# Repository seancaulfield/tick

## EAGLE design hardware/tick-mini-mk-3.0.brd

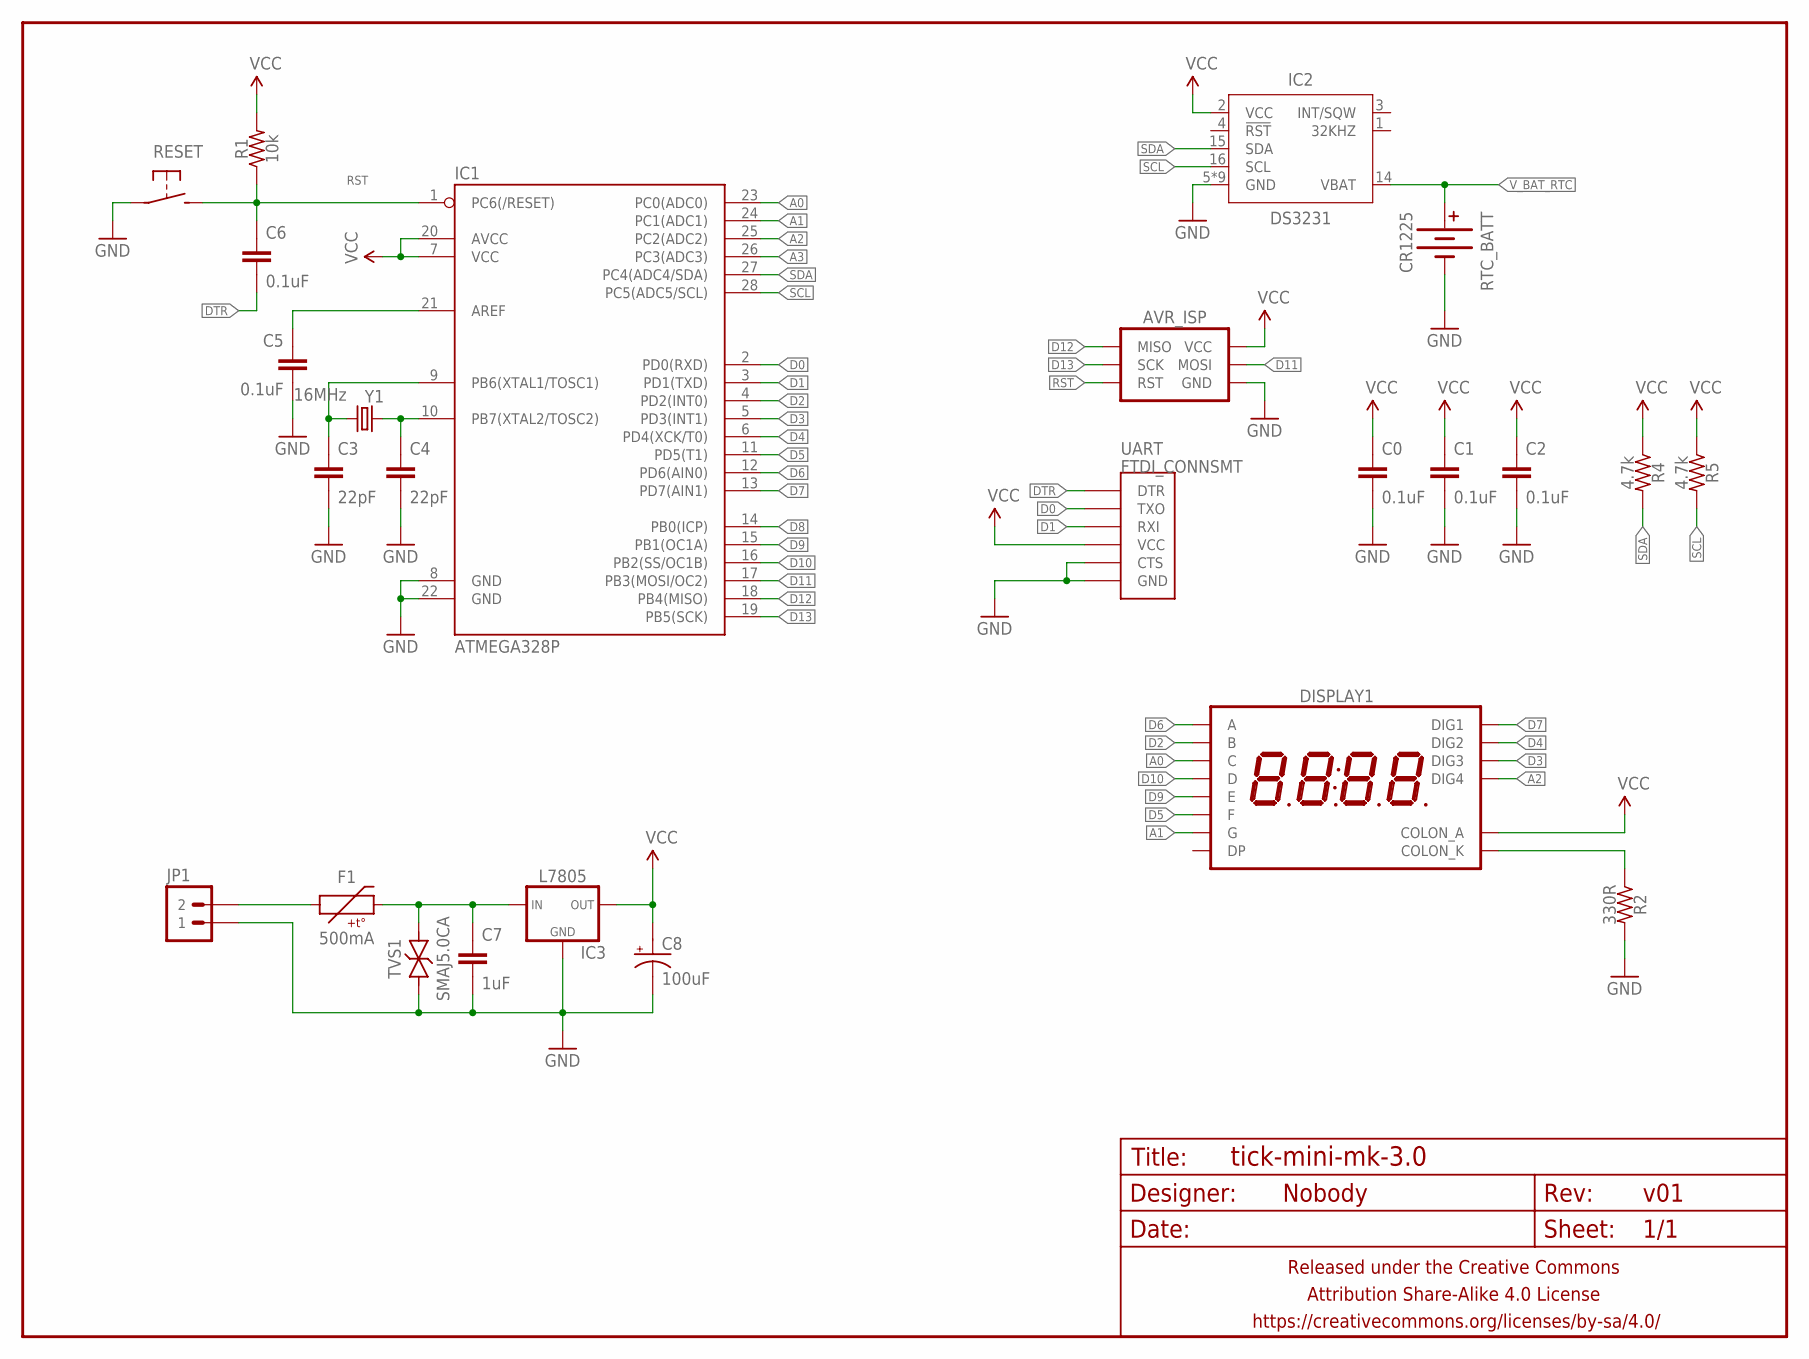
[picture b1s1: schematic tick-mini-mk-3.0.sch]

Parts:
AVR_ISP: AVR_SPI_PRG_6PTH; 2X3
C0, C1, C2, C5, C6: 0.1uF; C0603
C3, C4: 22pF; C0603
C7: 1uF; C0805
C8: 100uF; E2,5-5
DISPLAY1: 7SEG_4DIGIT_COLON14.2MM-CC-NS; 7SEG_4DIG_NS
F1: 500mA; PTC-1206
FRAME1: FRAME-LETTERNO_PACKAGE; DUMMY
IC1: ATMEGA328P; DIL28-3
IC2: DS3231; SO16W
IC3: L7805; SO08
JP1: M02PTH-CENTERED-R+; 1X02-CENTER-R+
R1: 10k; R0603
R2: 330R; RESISTOR-AXIAL-PTH-7.62MM
R4, R5: 4.7k; R0603
RESET: SPST-NO-TACT3MM-PTH-SMALL-PADS; DTS-3-SMALL-PADS
RTC_BATT: CR1225; BATTCON_12MM
TVS1: SMAJ5.0CA; SMA-DIODE-TVS-BIDIR
UART: FTDI_CONNSMT; FTDI_CONN_SMT
Y1: 16MHz; HC49U-V

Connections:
A0: DISPLAY1.P$4 (C), IC1.23 (PC0(ADC0))
A1: DISPLAY1.P$5 (G), IC1.24 (PC1(ADC1))
A2: DISPLAY1.P$6 (DIG4), IC1.25 (PC2(ADC2))
A3: IC1.26 (PC3(ADC3))
D0: IC1.2 (PD0(RXD)), UART.TXO
D1: IC1.3 (PD1(TXD)), UART.RXI
D2: DISPLAY1.P$9 (B), IC1.4 (PD2(INT0))
D3: DISPLAY1.P$10 (DIG3), IC1.5 (PD3(INT1))
D4: DISPLAY1.P$11 (DIG2), IC1.6 (PD4(XCK/T0))
D5: DISPLAY1.P$12 (F), IC1.11 (PD5(T1))
D6: DISPLAY1.P$13 (A), IC1.12 (PD6(AIN0))
D7: DISPLAY1.P$14 (DIG1), IC1.13 (PD7(AIN1))
D8: IC1.14 (PB0(ICP))
D9: DISPLAY1.P$1 (E), IC1.15 (PB1(OC1A))
D10: DISPLAY1.P$2 (D), IC1.16 (PB2(SS/OC1B))
D11: AVR_ISP.4 (MOSI), IC1.17 (PB3(MOSI/OC2))
D12: AVR_ISP.1 (MISO), IC1.18 (PB4(MISO))
D13: AVR_ISP.3 (SCK), IC1.19 (PB5(SCK))
DTR: C6.2, UART.DTR
GND: AVR_ISP.6 (GND), C0.2, C1.2, C2.2, C3.2, C4.2, C5.2, C7.2, C8.-, IC1.8 (GND), IC1.22 (GND), IC2.5 (GND), IC2.6 (GND), IC2.7 (GND), IC2.8 (GND), IC2.9 (GND), IC2.10 (GND), IC2.11 (GND), IC2.12 (GND), IC2.13 (GND), IC3.2 (GND), IC3.3 (GND), IC3.4 (GND), IC3.5 (GND), IC3.6 (GND), IC3.7 (GND), JP1.1, R2.P$2 (2), RESET.1, RTC_BATT.GND (-), TVS1.1, UART.CTS, UART.GND
unnamed: C4.1, IC1.10 (PB7(XTAL2/TOSC2)), Y1.1
unnamed: C3.1, IC1.9 (PB6(XTAL1/TOSC1)), Y1.2
unnamed: C5.1, IC1.21 (AREF)
unnamed: DISPLAY1.P$7 (COLON_K), R2.P$1 (1)
unnamed: F1.1, JP1.2
unnamed: C7.1, F1.2, IC3.8 (IN), TVS1.2
RST: AVR_ISP.5 (RST), C6.1, IC1.1 (PC6(/RESET)), R1.1, RESET.2
SCL: IC1.28 (PC5(ADC5/SCL)), IC2.16 (SCL), R5.2
SDA: IC1.27 (PC4(ADC4/SDA)), IC2.15 (SDA), R4.2
VCC: AVR_ISP.2 (VCC), C0.1, C1.1, C2.1, C8.+, DISPLAY1.P$8 (COLON_A), IC1.7 (VCC), IC1.20 (AVCC), IC2.2 (VCC), IC3.1 (OUT), R1.2, R4.1, R5.1, UART.VCC
V_BAT_RTC: IC2.14 (VBAT), RTC_BATT.PWR@1 (+)

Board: 2 copper layers, 26 parts (2 on the bottom side), 29 nets, no tracks yet.

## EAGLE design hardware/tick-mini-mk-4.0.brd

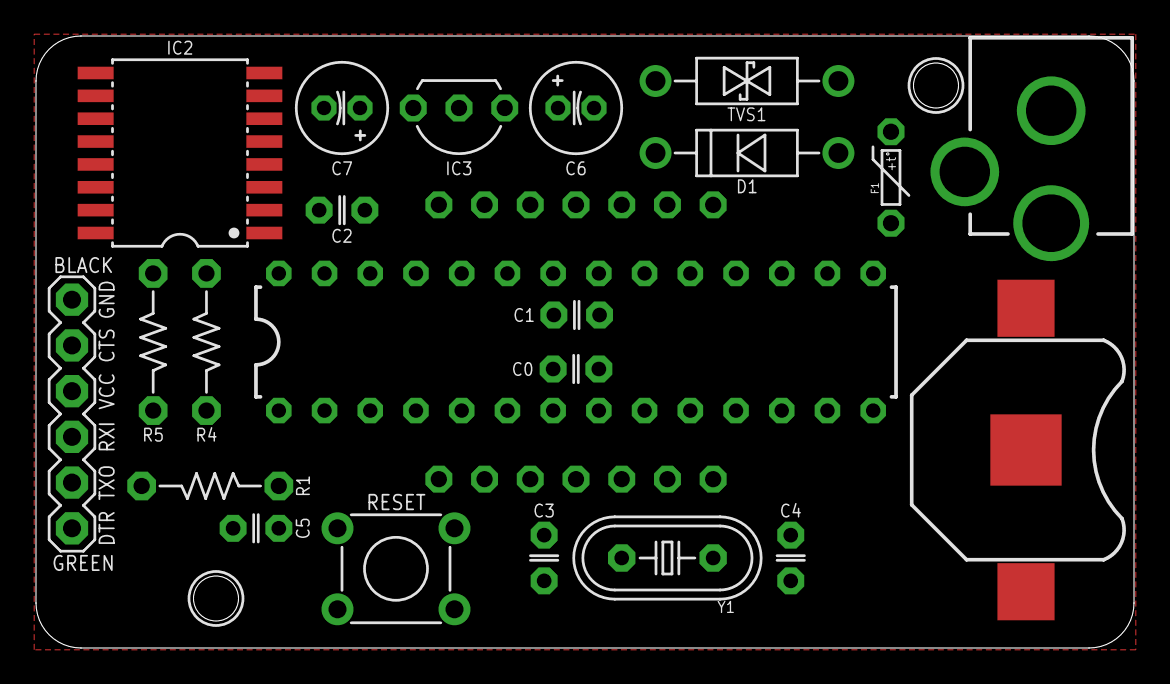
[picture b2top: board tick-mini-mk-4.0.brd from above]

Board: 2 copper layers, 61.0 x 34.0 mm, 24 parts (0 on the bottom side), 27 nets, no tracks yet.

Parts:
C0, C1, C2, C5: 0.1uF; C025-024X044
C3, C4: 22pF; C025-024X044
C6, C7: 10uF; E2-5
D1: 1N5819; DIODE-10.16MM
DISPLAY1: 7SEG_4DIGIT_COLON14.2MM-CC-NS; 7SEG_4DIG_NS
F1: 500mA; PTC-PTH-5.08MM
FRAME1: FRAME-LETTERNO_PACKAGE; DUMMY
IC1: ATMEGA328P; DIL28-3
IC2: DS3231; SO16W
IC3: L7805; TO-92-AMMO
PWR1: DCBARRELPTH; DCJACK_2MM_PTH
R1: 10k; RESISTOR-AXIAL-PTH-7.62MM
R4, R5: 4.7k; RESISTOR-AXIAL-PTH-7.62MM
RESET: SPST-NO-TACT6MM-PTH-SMALL-PADS; DTS-6-SMALL-PADS
RTC_BATT: CR1225; BATTCON_12MM
TVS1: SMAJ5.0CA; DO-41-TVS-BI-10.16MM
UART: FTDI_CONNFLIPPER; FTDI_CONN_FLIP
Y1: 16MHz; HC49U-V

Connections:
A0: DISPLAY1.P$4, IC1.23
A1: DISPLAY1.P$3, IC1.24
A2: DISPLAY1.P$2, IC1.25
A3: DISPLAY1.P$1, IC1.26
D0: IC1.2, UART.TXO
D1: IC1.3, UART.RXI
D2: DISPLAY1.P$14, IC1.4
D3: DISPLAY1.P$13, IC1.5
D4: DISPLAY1.P$12, IC1.6
D5: DISPLAY1.P$11, IC1.11
D6: DISPLAY1.P$10, IC1.12
D7: DISPLAY1.P$9, IC1.13
D11: DISPLAY1.P$7, IC1.17
D12: DISPLAY1.P$6, IC1.18
D13: DISPLAY1.P$5, IC1.19
DTR: C5.2, UART.DTR
GND: C0.2, C1.2, C2.2, C3.2, C4.2, C6.-, C7.-, IC1.8, IC1.22, IC2.5, IC2.6, IC2.7, IC2.8, IC2.9, IC2.10, IC2.11, IC2.12, IC2.13, IC3.2, PWR1.BRK, RTC_BATT.GND, TVS1.P$1, UART.CTS, UART.GND
unnamed: C4.1, IC1.10, Y1.1
unnamed: C3.1, IC1.9, Y1.2
unnamed: D1.A, F1.P$2, TVS1.P$2
unnamed: F1.P$1, PWR1.PWR
unnamed: C6.+, D1.C, IC3.1
RST: C5.1, IC1.1, R1.P$1, RESET.1, RESET.2
SCL: IC1.28, IC2.16, R5.P$2
SDA: IC1.27, IC2.15, R4.P$2
VCC: C0.1, C1.1, C2.1, C7.+, DISPLAY1.P$8, IC1.7, IC1.20, IC2.2, IC3.3, R1.P$2, R4.P$1, R5.P$1, UART.VCC
V_BAT_RTC: IC2.14, RTC_BATT.PWR@1

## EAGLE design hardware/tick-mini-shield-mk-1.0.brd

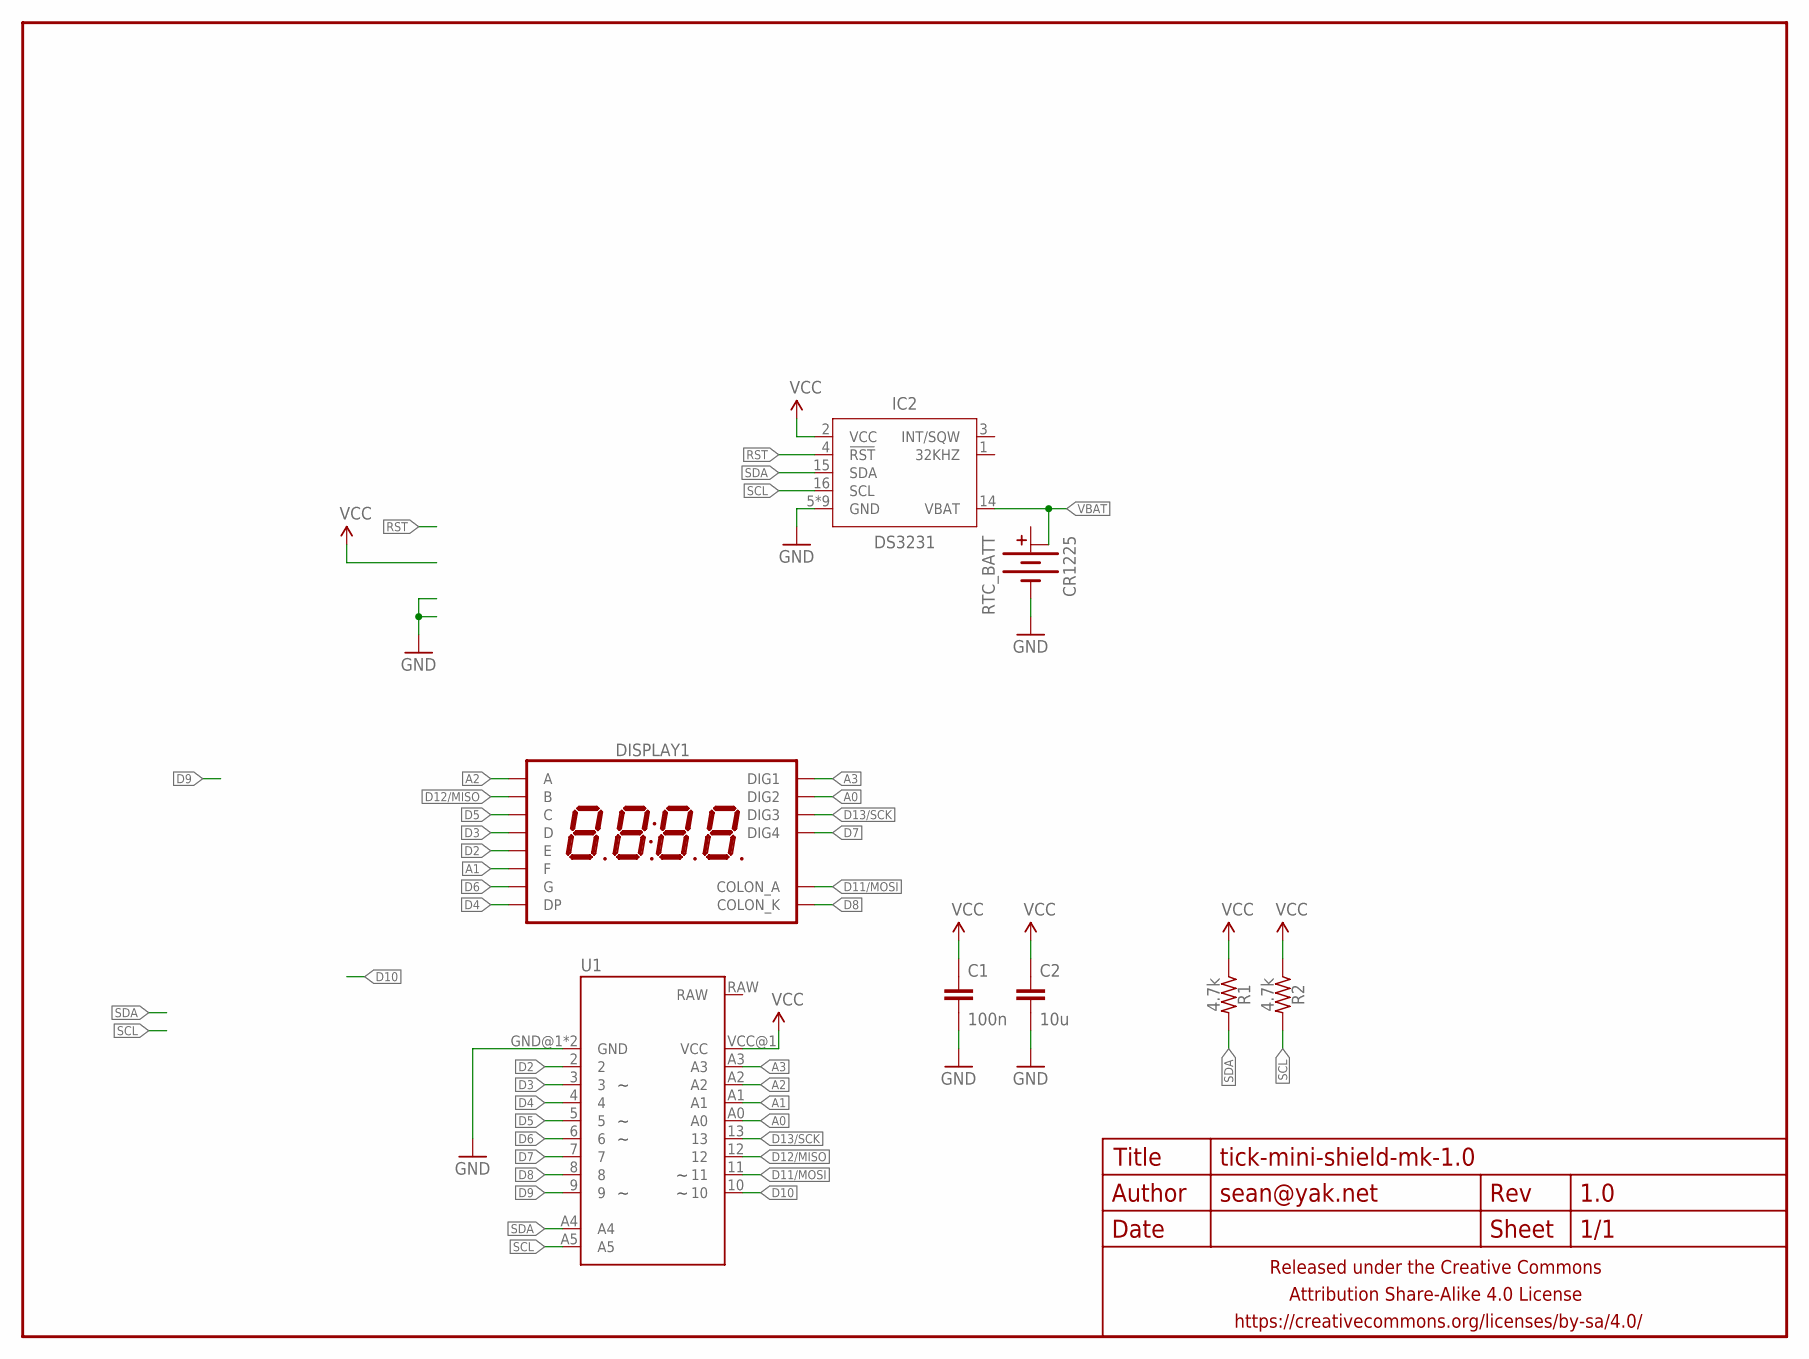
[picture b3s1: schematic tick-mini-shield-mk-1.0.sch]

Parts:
C1: 100n; C025-024X044
C2: 10u; C050-025X075
DISPLAY1: 7SEG_4DIGIT_COLONTICK; 7SEG_4DIG_TICK
FRAME1: FRAME-LETTERNO_PACKAGE; DUMMY
IC2: DS3231; SO16W
R1, R2: 4.7k; RESISTOR-AXIAL-PTH-7.62MM
RTC_BATT: CR1225; BATTCON_12MM_PTH3
U1: ARDUINO_PRO_MINI_TICK2

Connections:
A0: DISPLAY1.P$11 (DIG2), U1.A0
A1: DISPLAY1.P$12 (F), U1.A1
A2: DISPLAY1.P$13 (A), U1.A2
A3: DISPLAY1.P$14 (DIG1), U1.A3
D2: DISPLAY1.P$1 (E), U1.2
D3: DISPLAY1.P$2 (D), U1.3
D4: DISPLAY1.P$3 (DP), U1.4
D5: DISPLAY1.P$4 (C), U1.5
D6: DISPLAY1.P$5 (G), U1.6
D7: DISPLAY1.P$6 (DIG4), U1.7
D8: DISPLAY1.P$7 (COLON_K), U1.8
D9: U1.9
D10: U1.10
D11/MOSI: DISPLAY1.P$8 (COLON_A), U1.11
D12/MISO: DISPLAY1.P$9 (B), U1.12
D13/SCK: DISPLAY1.P$10 (DIG3), U1.13
GND: C1.2, C2.2, IC2.5 (GND), IC2.6 (GND), IC2.7 (GND), IC2.8 (GND), IC2.9 (GND), IC2.10 (GND), IC2.11 (GND), IC2.12 (GND), IC2.13 (GND), RTC_BATT.-, U1.GND@1 (GND), U1.GND@2 (GND)
RST: IC2.4 (!RST)
SCL: IC2.16 (SCL), R2.P$2 (2), U1.A5
SDA: IC2.15 (SDA), R1.P$2 (2), U1.A4
VBAT: IC2.14 (VBAT), RTC_BATT.+@3 (+1), RTC_BATT.+@4 (+1)
VCC: C1.1, C2.1, IC2.2 (VCC), R1.P$1 (1), R2.P$1 (1), U1.VCC@1 (VCC)

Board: 2 copper layers, 12 parts (5 on the bottom side), 19 nets, no tracks yet.

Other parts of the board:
U$4: CC-BY-SA-4.0-NO-URL
U$7, U$8: OSHWLOGO_TOP_0.2_A

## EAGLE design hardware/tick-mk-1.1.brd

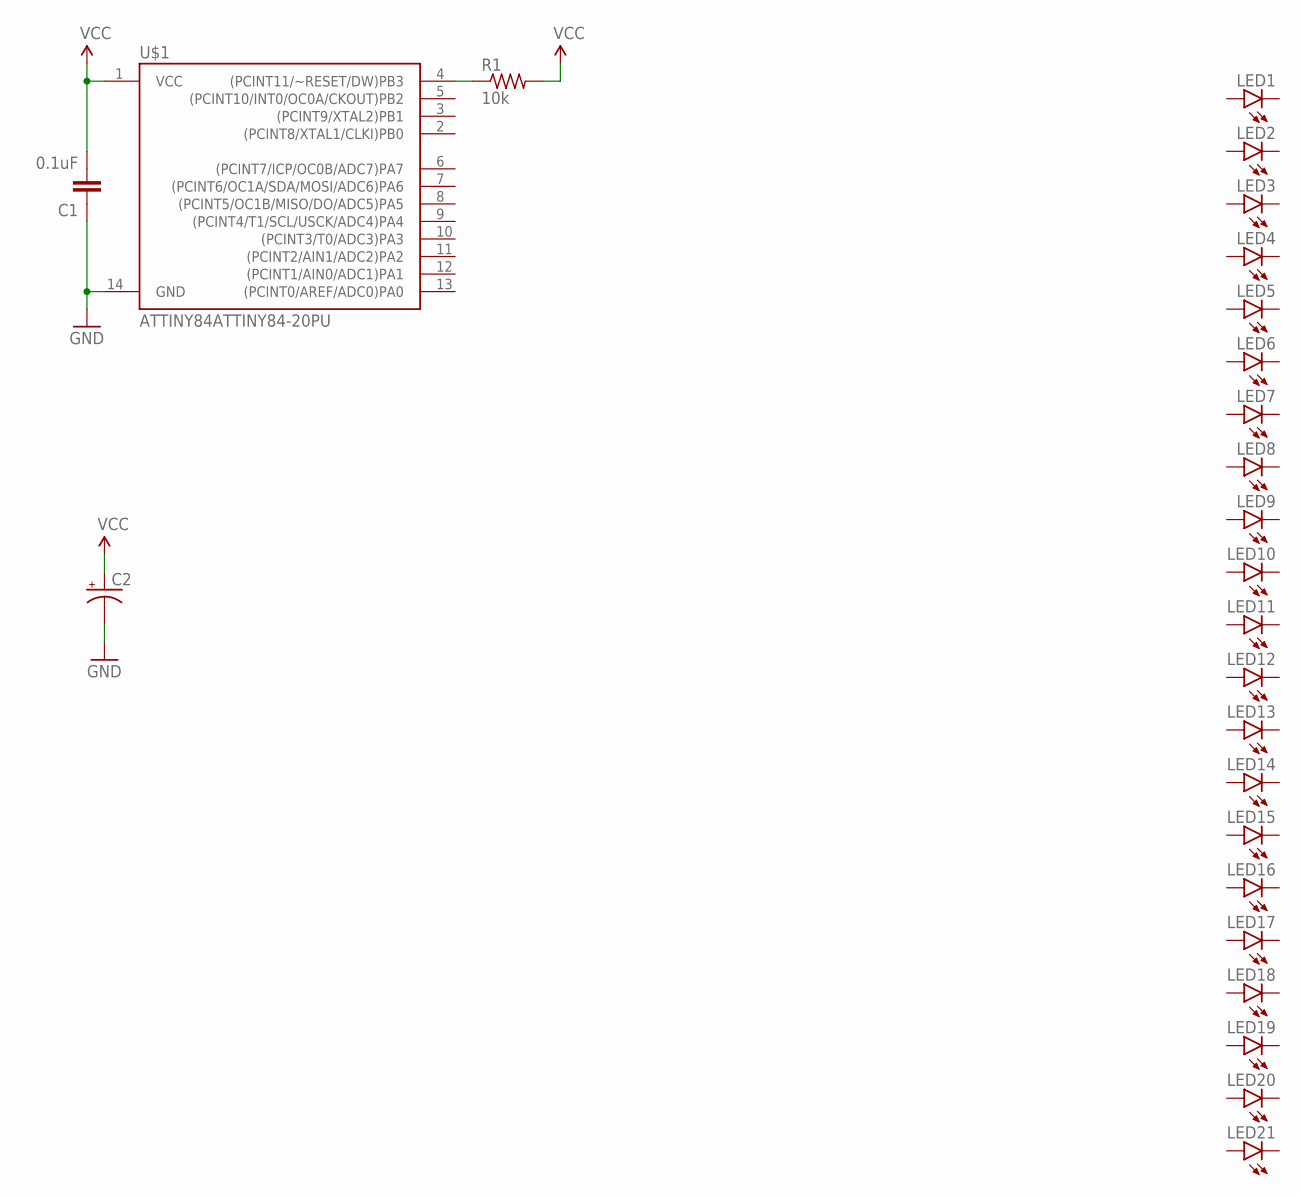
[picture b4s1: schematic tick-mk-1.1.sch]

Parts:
C1: 0.1uF; C025-024X044
C2: CAPACITOR-POLARIZEDE2-5; E2-5
LED1, LED2, LED3, LED4, LED5, LED6, LED7, LED8, LED9, LED10, LED11, LED12, LED13, LED14, LED15, LED16, LED17, LED18, LED19, LED20, LED21: LED5MM_SHORTPADS
R1: 10k; RESISTOR-AXIAL-PTH-5.08MM
U$1: ATTINY84ATTINY84-20PU; DIL14

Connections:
GND: C1.1, C2.-, U$1.14 (GND)
unnamed: R1.P$1 (1), U$1.4 ((PCINT11/~RESET/DW)PB3)
VCC: C1.2, C2.+, R1.P$2 (2), U$1.1 (VCC)

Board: 2 copper layers, 25 parts (0 on the bottom side), 3 nets, no tracks yet.

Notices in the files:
parts and their libraries:
A_butts: Released under the Creative Commons Attribution Share-Alike 4.0 License
A_butts: https://creativecommons.org/licenses/by-sa/4.0
A_butts: Released under the Creative Commons
